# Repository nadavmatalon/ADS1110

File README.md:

# ADS1110 DRIVER

&nbsp;&nbsp;&nbsp;&nbsp;&nbsp;&nbsp;&nbsp;&nbsp;&nbsp;&nbsp;

&nbsp;&nbsp;&nbsp;&nbsp;&nbsp;&nbsp;&nbsp;&nbsp;&nbsp;&nbsp;

&nbsp;&nbsp;&nbsp;&nbsp;&nbsp;&nbsp;&nbsp;&nbsp;&nbsp;&nbsp;

The ADS1110 is a 16-Bit Single-Channel (Single-Ended or Differential) ADC with Onboard Reference (2.048V), PGA & HW I2C capabilities.

This library contains a complete driver for the ADS1110 offering full control over its Configuration Settings, as well as the ability to recieve raw data, voltage readings (in mV, to avoid floating point math) or percentage readings in either Single-Shot or Continuous mode.

Source: [ADS1110 DATASHEET](http://www.ti.com/lit/ds/symlink/ads1110.pdf)

## Repository Contents

- **ADS1110.h** - Library Header file.
- **ADS1110.cpp** - Library Compilation.
- **/utility** 
  - **ADS1110InfoStr.h** - Header file containing a functional extention of the library to include generating printable information String (see Note #5 below).
  - **ADS1110ComStr.h** - Header file containing a functional extention of the library to include generating a printable I2C Communication Result String (see Note #6 below).
  - **ADS1110_PString.h** - Header file for PString class (lighter alternative to String class) 
  - **ADS1110_PString.cpp** - Compilation file for PString class (lighter alternative to String class) 
- **/examples**   
  - **/ADS1110_Test**
    - **ADS1110_Test.ino** - A basic sketch for testing whether the ADS1110 is hooked-up and operating correctly.
  - **/ADS1110_Usage**
    - **ADS1110_Usage.ino** - A much more extensive sketch offering a complete usage illustration, as well as a rubust testing mechanism.
  - **/ADS1110_Info** 
    - **ADS1110_Info.ino** - A short sketch showing how to generate a Printable Device Information String of the ADS1110's current settings (i.e. Configuration, Limit &anp; Hysteresis registers, etc.).
  - **/ADS1110_I2C_Status**
    - **ADS1110_I2C_Status.ino** - A short sketch for verifying I2C communication has been established between the controller and the ADS1110.
- **/extras**
  - **License.txt** - A cope of the end-user license agreement.  
  - **/eagle**
    - **ADS1110.sch** - Schematic file for the ADS1110 breakout board.
    - **ADS1110.brd** - Board layout file for the ADS1110 breakout board.
  - **/images**
    - **ads1110_pinout.png** - Pinout image of the ADS1110.
- **keywords.txt** - Keywords for this library which will be highlighted in sketches within the Arduino IDE. 
- **library.properties** - General library properties for the Arduino's IDE (>1.5) Library Package Manager.
- **README.md** - The readme file for this library.
- **library.json** - JSON file for the Arduino's IDE (>1.5) Package Manager.

## HOOK-UP

* __PIN 1 (Vin+)__ - Connect Vin+ to voltage source to be measured
* __PIN 2 (GND)__ - Connect GND to Arduino GND
* __PIN 3 (SCL)__ - Connect to Arduino PIN A5 with a 2K2 pull-up resistor
* __PIN 4 (SDA)__ - Connect to the Arduino's PIN A5 with a 2K2 pull-up resistor
* __PIN 5 (VCC)__ - Connect VCC to Arduino 5V output
* __PIN 6 (Vin-)__ - Connect Vin- either to Arduino GND (for Single-Ended voltage readings ranging 0-2.048V) or to an external 2.048V reference source (for Single-Ended voltage readings ranging 0-4.096V) or to 'negative' input (for differential voltage readings between positive and 'negative' inputs).
* __DECOUPING__: Connect a 0.1uF Ceramic Capacitor between the ADS1110's VCC &amp; GND PINS

>__Note__: The 'negative' of input Vin- is put in brackets here because it actually differential in nature and not a so-called real negative voltage - 
that is, it's negative only with relation to the positive input side of Vin+.

## GENERAL NOTES

1) __I2C Communications Library Dependency__

This library depends on the Arduino IDE's native '[Wire](https://github.com/arduino/Arduino/tree/master/hardware/arduino/avr/libraries/Wire)' library for I2C communication between the Arduino (Master) and the ADS1110 (Slave). 

2) __Dangers of GAIN Setting__

As I've managed to fry 2 ADS1110 ICs by changing the GAIN settings from the default x1 to another value, I've decided to stay away from this particular setting and not to include it in the full usage/testing sketch. That said, the library does contain the relevant functions for getting/setting the GAIN, however, make sure you know what you're doing when fiddling with this as you may damage your device.

3) __Voltage Reference Settings__

To get the correct __Raw Data Reading__/__Voltage Readings__/__Percentage Readings__, it is crucial to have the __Voltage Reference (Vref)__ setting defined correctly (i.e. INTERNAL / EXTERNAL). This is done on the basis of the physical hookup of the ADS1110's pin Vin- (namely: INTERNAL if this pin goes to GND, or EXTERNAL if it goes to an 2.048V external source. The default is GND connection &amp; an INTERNAL settings definition).  

4) __Sample Rate &amp; Resolution Interdependence__

The ADS1110's __Sample Rate__ and __Resolution__ settings are interdependent, that is, setting the value of one will automatically cause the other to change accordingly (15_SPS = 16-BIT / 30_SPS = 15-BIT / 60_SPS = 14-BIT / 240_SPS = 12-BIT).  

5) __Device Information String__

It possible to extend the ADS1110 Library to include a function for generating a printable device information string showing all the relevant details about the devices current Configuration, Limit & Hysteresis settings. As the additional functionality comes at the cost of increased memory footprint, it was implemented as an optional add-on rather than added directly to the core ADS1110 Library. See the [ADS1110_Info](https://github.com/nadavmatalon/ADS1110/blob/master/examples/ADS1110_Info/ADS1110_Info.ino) example sketch for detailed explanation and an actual usage demo.

6) __Device I2C Communications String__

It is also possible to extend the ADS1110 Library to include a function for generating a printable I2C Communications string showing the result of each I2C transaction in a human-friendly way, something that may be useful, for example, during debugging sessions. As the additional functionality comes at the cost of increased memory footprint, it was implemented as an optional add-on rather than added directly to the core ADS1110 Library. See the [ADS1110_I2C_Status](https://github.com/nadavmatalon/ADS1110/blob/master/examples/ADS1110_I2C_Status/ADS1110_I2C_Status.ino) example sketch for detailed explanation and an actual usage demo.

## I2C ADDRESSES

Each ADS1110 has 1 of 8 possible I2C addresses (factory hardwired &amp; recognized by its specific part number & top marking on the package itself):

| PART NO.  | BIN     | HEX  | DEC | MARKING |
|-----------|---------|------|-----|---------|
| ADS1110A0 | 1001000 | 0x48 | 72  | ED0     |
| ADS1110A1 | 1001001 | 0x49 | 73  | ED1     |
| ADS1110A2 | 1001010 | 0x4A | 74  | ED2     |
| ADS1110A3 | 1001011 | 0x4B | 75  | ED3     |
| ADS1110A4 | 1001100 | 0x4C | 76  | ED4     |
| ADS1110A5 | 1001101 | 0x4D | 77  | ED5     |
| ADS1110A6 | 1001110 | 0x4E | 78  | ED6     |
| ADS1110A7 | 1001111 | 0x4F | 79  | ED7     |

## LIBRARY INSTALLATION & SETUP

Begin by installing the library either by using the Arduino IDE's Installation Wizard (Arduino Version >1.5) or simply download the library's ZIP folder from GITHUB, extract it, and copy the extraxcted folder to your Arduino 'libraries' folder.

Next, include the library at the top of the sketch as follows:

```
#include "ADS1110.h"
```

At this point you can construct a new ADS1110 object(s) by using the following command (at the top of the sketch after the 'include' line):

```
ADS1110 device_name(device_address);
```

>Replace '__device_name__' with a name of your choice. Also, make sure to replace the variable '__device_address__' with 
the specific I2C address of your device if needed (see I2C ADDRESSES section above).

Next, make sure to inlude an instruction for initializing the I2C Bus for the [Wire](https://github.com/arduino/Arduino/tree/master/hardware/arduino/avr/libraries/Wire) Library, as follows:

(There's no need to include the [Wire](https://github.com/arduino/Arduino/tree/master/hardware/arduino/avr/libraries/Wire) Library at the top of the sketch as it's already included by the present library)

```
void setup() {
    Wire.begin();
    // ...other setup code...
}
```

## LIBRARY FUNCTIONS

With the library installed &amp; included in the sketch, and an ADS1110 object initiallized, the following functions are available (see the usage example sketch for a detailed implementation):

__Note About Methods' Return Values:__  
All 'get' methods return some sort of value (e.g. getGain(), getMode() etc.), while all 'set' methods return nothing. Nevertheless, ALL methods implicitly update the library's __I2C _comBuffer__ (=communication buffer) after each I2C transmission. The reason for this functional design is to maintain structural coherance between the 'get' and 'set' methods. As 'get' methods cannot return both the desired value and the I2C transmission's result simultaniously. Consequently, if the relevant value hasn't been obtained by a particular 'get' method, the user can simply check the content of the _comBuffer to see what error occured. Similarly, it is possible to check if a particular setting has been successfully applied via a 'set' method either by preforming the corresponding 'get' method or by checking the content of the _comBuffer (0 indicates a successful transmission, 1-6 indicate an error as listed below). 

__ping();__                                    
Parameters:&nbsp;&nbsp;&nbsp;None  
Description:&nbsp;&nbsp;&nbsp;Searches for the ADS1110 at the pre-defined I2C Bus address &amp; returns byte with the relevant success/error code, as follows:  
0  ...  Success (no error)  
1  ...  Buffer overflow  
2  ...  Address sent, NACK received  
3  ...  Data send, NACK received  
4  ...  Other error (lost bus arbitration, bus error, etc.)  
5  ...  Timed-out while trying to become Bus Master  
6  ...  Timed-out while waiting for data to be sent  
\>6 ... Unlisted error (potential future implementation/s)<br>
Returns:&nbsp;&nbsp;&nbsp;&nbsp;&nbsp;&nbsp;&nbsp;&nbsp;&nbsp;byte  
  
__getGain();__  
Parameters:&nbsp;&nbsp;&nbsp;None  
Description:&nbsp;&nbsp;&nbsp;Gets the current Gain settings (x1 [Default] / x2 / x4 / x8)  
Returns:&nbsp;&nbsp;&nbsp;&nbsp;&nbsp;&nbsp;&nbsp;&nbsp;Byte  
  
__getSampleRate();__  
Parameters:&nbsp;&nbsp;&nbsp;None  
Description:&nbsp;&nbsp;&nbsp;Gets the current Sample Rate settings  (15 SPS [Default] / 30 SPS / 60 SPS / 240 SPS)  
Returns:&nbsp;&nbsp;&nbsp;&nbsp;&nbsp;&nbsp;&nbsp;&nbsp;Byte  
  
__getConMode();__  
Parameters:&nbsp;&nbsp;&nbsp;None  
Description:&nbsp;&nbsp;&nbsp;Gets the current Conversion Mode settings (0 = CONTINUOUS [Default] / 1 = SINGLE-SHOT)  
Returns:&nbsp;&nbsp;&nbsp;&nbsp;&nbsp;&nbsp;&nbsp;&nbsp;Byte  
  
__getRes();__  
Parameters:&nbsp;&nbsp;&nbsp;None  
Description:&nbsp;&nbsp;&nbsp;Gets the current Resolution settings (12-BIT / 14-BIT / 15-BIT / 16-BIT [Default])  
Returns:&nbsp;&nbsp;&nbsp;&nbsp;&nbsp;&nbsp;&nbsp;&nbsp;Byte  
  
__getVref();__  
Parameters:&nbsp;&nbsp;&nbsp;None  
Description:&nbsp;&nbsp;&nbsp;Gets the current Voltage Reference mode (0 = INTERNAL [Default] / 2048 = EXTERNAL)  
Returns:&nbsp;&nbsp;&nbsp;&nbsp;&nbsp;&nbsp;&nbsp;&nbsp;Int  
  
__setGain();__  
Parameters:&nbsp;&nbsp;&nbsp;GAIN_1 / GAIN_2 /GAIN_4 / GAIN_8  
Description:&nbsp;&nbsp;&nbsp;Sets the Gain (x1 / x2 / x4 / x8)  
Returns:&nbsp;&nbsp;&nbsp;&nbsp;&nbsp;&nbsp;&nbsp;&nbsp;None  
  
__setSampleRate();__  
Parameters:&nbsp;&nbsp;&nbsp;SPS_15 / SPS_30 / SPS_60 / SPS_240  
Description:&nbsp;&nbsp;&nbsp;Sets the Sample Rate in Samples per Second (15 SPS / 30 SPS / 60 SPS / 240 SPS)  
Returns:&nbsp;&nbsp;&nbsp;&nbsp;&nbsp;&nbsp;&nbsp;&nbsp;None  
  
__setConMode();__  
Parameters:&nbsp;&nbsp;&nbsp;CONT / SINGLE  
Description:&nbsp;&nbsp;&nbsp;Sets the Conversion Mode (CONTINUOUS / SINGLE-SHOT)  
Returns:&nbsp;&nbsp;&nbsp;&nbsp;&nbsp;&nbsp;&nbsp;&nbsp;None  
  
__setRes();__  
Parameters:&nbsp;&nbsp;&nbsp;12_BIT / 14_BIT / 15_BIT / 16_BIT  
Description:&nbsp;&nbsp;&nbsp;Sets the Resolution level ( 12-BIT / 14-BIT / 15-BIT / 16-BIT)  
Returns:&nbsp;&nbsp;&nbsp;&nbsp;&nbsp;&nbsp;&nbsp;&nbsp;None  
  
__setVref();__  
Parameters:&nbsp;&nbsp;&nbsp;INT_REF / EXT_REF  
Description:&nbsp;&nbsp;&nbsp;Sets the Voltage reference mode (INTERNAL / EXTERNAL)  
This setting needs to be set according to the hardware hookup of the ADS1110 Pin Vin-, namely: If the Vin- pin is connected to GND, then the Voltage Reference (Vref) should be set to 'INTERNAL'. This, in turn, provides a voltage reading range of 0-2048mV. Alternatively, the Vin- pin may be connected to an external 2.048V source, in which case the Voltage Referece settings should be set to 'EXTERNAL'. The latter hookup & setting gives an extended voltage reading range of 0-4096mV.  
Returns:&nbsp;&nbsp;&nbsp;&nbsp;&nbsp;&nbsp;&nbsp;&nbsp;None  
  
__reset();__  
Parameters:&nbsp;&nbsp;&nbsp;None  
Description:&nbsp;&nbsp;&nbsp;Resets the Configuration register to its default settings  
Returns:&nbsp;&nbsp;&nbsp;&nbsp;&nbsp;&nbsp;&nbsp;&nbsp;None  
  
__getData();__  
Parameters:&nbsp;&nbsp;&nbsp;None  
Description:&nbsp;&nbsp;&nbsp;Gets the latest raw ADC reading  
Returns:&nbsp;&nbsp;&nbsp;&nbsp;&nbsp;&nbsp;&nbsp;&nbsp;Int  
  
__getVolt();__  
Parameters:&nbsp;&nbsp;&nbsp;None  
Description:&nbsp;&nbsp;&nbsp;Gets the latest ADC reading (in mV, to avoid floating point calculations)  
Returns:&nbsp;&nbsp;&nbsp;&nbsp;&nbsp;&nbsp;&nbsp;&nbsp;Int  
  
__getPercent();__  
Parameters:&nbsp;&nbsp;&nbsp;None  
Description:&nbsp;&nbsp;&nbsp;Gets the latest ADC reading in Percentage format (0-100%)  
Returns:&nbsp;&nbsp;&nbsp;&nbsp;&nbsp;&nbsp;&nbsp;&nbsp;Byte  
  
__getComResult();__  
Parameters:&nbsp;&nbsp;&nbsp;None  
Description:&nbsp;&nbsp;Returns the latest I2C Communication result code (see Success/Error codes above)  
Returns:&nbsp;&nbsp;&nbsp;&nbsp;&nbsp;&nbsp;&nbsp;&nbsp;byte  
  
__Destructor__  
If you want to destruct an instantiated ADS1110 object, you can use the following method to do so:  

```
~ADS1110 device_name();
```
>Replace '__device_name__' with the name of your ADS1110 device.

## Extended Functionality*

(* requires an additional '\#include' of the relevant *.h file as shown in the corresponding example sketches)  
  
__ADS1110ComStr();__  
Parameters:&nbsp;&nbsp;&nbsp;Name of an initialized ADS1110 instance  
Description:&nbsp;&nbsp;Returns printable string containing human-friendly information about the device's latest I2C communication result  
Returns:&nbsp;&nbsp;&nbsp;&nbsp;&nbsp;&nbsp;&nbsp;&nbsp;PString  
  
__ADS1110InfoStr();__  
Parameters:&nbsp;&nbsp;&nbsp;Name of an initialized ADS1110 instance  
Description:&nbsp;&nbsp;Returns printable string containing detailed information about the device's current settings  
Returns:&nbsp;&nbsp;&nbsp;&nbsp;&nbsp;&nbsp;&nbsp;&nbsp;PString  

## RUNNING THE EXAMPLE SKETCHES
  
1) Start the Arduino IDE and open the relevant example sketch  
2) Hook-up the ADS1110 to the Arduino as explained in the sketch's notes   
3) Upload the sketch to the Arduino  
4) Open the Serial Communications Window (make sure the baud-rate is set to 9600 or change it in the sketch to match your Serial Port's buad-rate)  
  
## BUG REPORTS
  
Please report any issues/bugs/suggestions at the [Issues](https://github.com/nadavmatalon/ADS1110/issues) section of this Github repository.
  
## TODO
  
* __CORE LIBRARY__: Add running average functionality  
  
## VERSION HISTORY

__Ver. 1.0.0__ - First release (26.9.16)  
__Ver. 1.1.0__ - Major code refactoring (10.10.16)  
__Ver. 1.2.0__ - Added namespaces to prevent conflicts with other libraries (15.10.16)  
__Ver. 1.3.0__ - Switched from 'WSWire' library to 'Wire' library for I2C communications (24.10.16)

## LICENSE

[The MIT License (MIT)](https://opensource.org/licenses/MIT)
Copyright (c) 2016 Nadav Matalon

Permission is hereby granted, free of charge, to any person obtaining a copy of this software and associated documentation files (the "Software"), to deal in the Software without restriction, including without limitation the rights to use, copy, modify, merge, publish, distribute, sublicense, and/or sell copies of the Software, and to permit persons to whom the Software is furnished to do so, subject to the following conditions:

The above copyright notice and this permission notice shall be included in all copies or substantial portions of the Software.

THE SOFTWARE IS PROVIDED "AS IS", WITHOUT WARRANTY OF ANY KIND, EXPRESS OR IMPLIED, INCLUDING BUT NOT LIMITED TO THE WARRANTIES OF MERCHANTABILITY, FITNESS FOR A PARTICULAR PURPOSE AND NONINFRINGEMENT. IN NO EVENT SHALL THE AUTHORS OR COPYRIGHT HOLDERS BE LIABLE FOR ANY CLAIM, DAMAGES OR OTHER LIABILITY, WHETHER IN AN ACTION OF CONTRACT, TORT OR OTHERWISE, ARISING FROM, OUT OF OR IN CONNECTION WITH THE SOFTWARE OR THE USE OR OTHER DEALINGS IN THE SOFTWARE.

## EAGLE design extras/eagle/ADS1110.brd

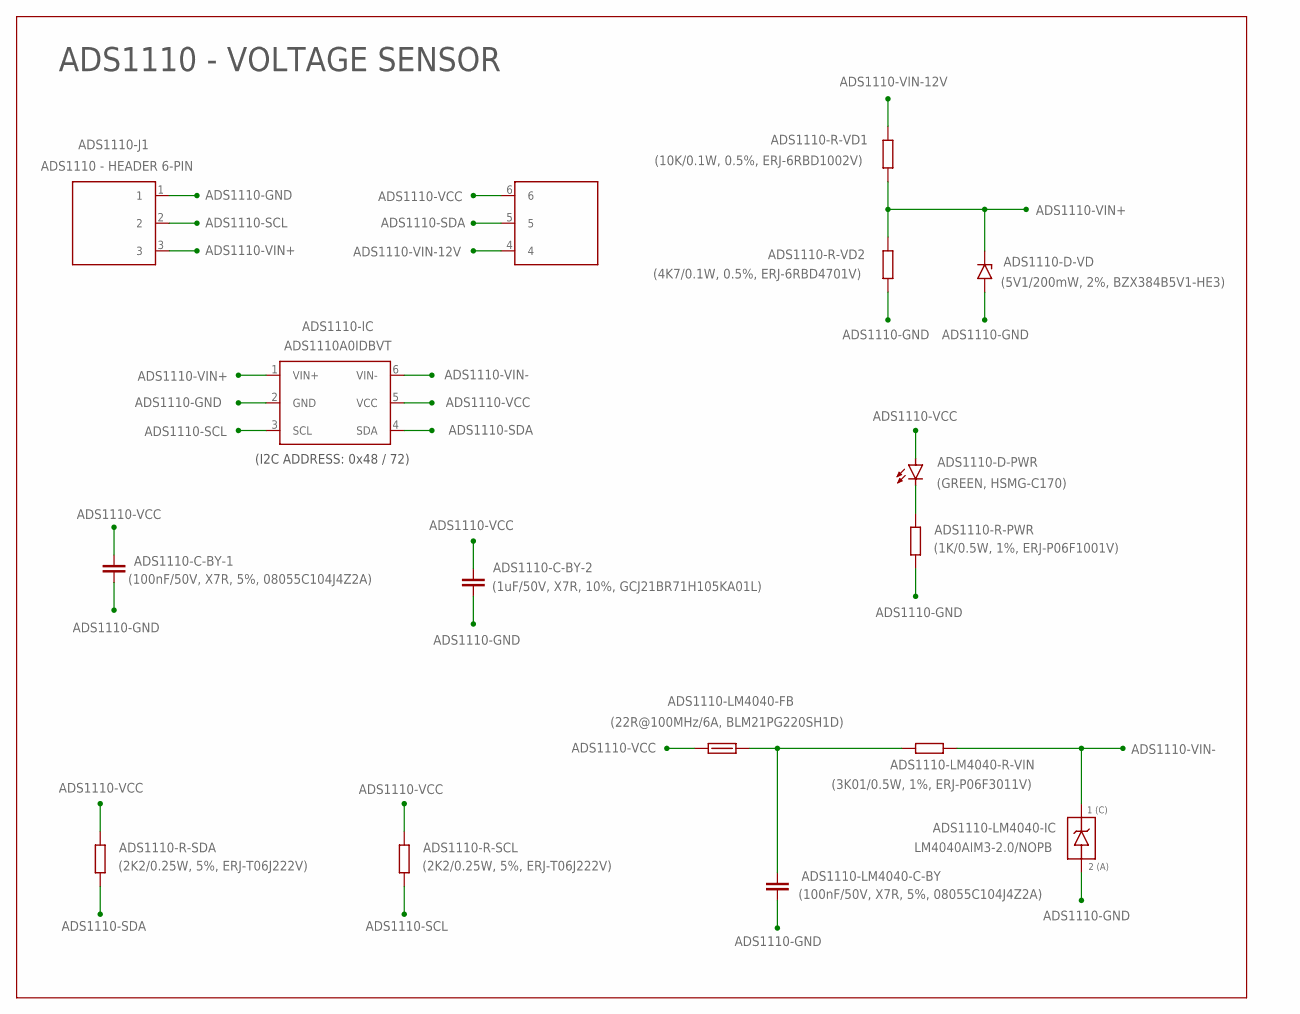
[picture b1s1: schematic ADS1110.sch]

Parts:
ADS1110-C-BY-1, ADS1110-LM4040-C-BY: (100nF/50V, X7R, 5%, 08055C104J4Z2A); 0805
ADS1110-C-BY-2: (1uF/50V, X7R, 10%, GCJ21BR71H105KA01L); 0805
ADS1110-D-PWR: (GREEN, HSMG-C170); DIODE_0805
ADS1110-D-VD: (5V1/200mW, 2%, BZX384B5V1-HE3); SOD-323-DIODE
ADS1110-IC: ADS1110A0IDBVT; SOT-457-6
ADS1110-J1: ADS1110 - HEADER 6-PIN; HEADER_2.54MM_6_PIN_VER
ADS1110-LM4040-FB: (22R@100MHz/6A, BLM21PG220SH1D); 0805
ADS1110-LM4040-IC: LM4040AIM3-2.0/NOPB; SOT-23-3
ADS1110-LM4040-R-VIN: (3K01/0.5W, 1%, ERJ-P06F3011V); 0805
ADS1110-R-PWR: (1K/0.5W, 1%, ERJ-P06F1001V); 0805
ADS1110-R-SCL, ADS1110-R-SDA: (2K2/0.25W, 5%, ERJ-T06J222V); 0805
ADS1110-R-VD1: (10K/0.1W, 0.5%, ERJ-6RBD1002V); 0805
ADS1110-R-VD2: (4K7/0.1W, 0.5%, ERJ-6RBD4701V); 0805

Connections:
ADS1110-GND: ADS1110-C-BY-1.2 (C), ADS1110-C-BY-2.1 (A), ADS1110-D-VD.A, ADS1110-IC.2 (GND), ADS1110-J1.1, ADS1110-LM4040-C-BY.2 (C), ADS1110-LM4040-IC.2 (A), ADS1110-LM4040-IC.3 (A), ADS1110-R-PWR.1, ADS1110-R-VD2.2
ADS1110-LED-PWR: ADS1110-D-PWR.C, ADS1110-R-PWR.2
ADS1110-SCL: ADS1110-IC.3 (SCL), ADS1110-J1.2, ADS1110-R-SCL.1
ADS1110-SDA: ADS1110-IC.4 (SDA), ADS1110-J1.5, ADS1110-R-SDA.1
ADS1110-VCC: ADS1110-C-BY-1.1 (A), ADS1110-C-BY-2.2 (C), ADS1110-D-PWR.A, ADS1110-IC.5 (VCC), ADS1110-J1.6, ADS1110-LM4040-FB.2, ADS1110-R-SCL.2, ADS1110-R-SDA.2
ADS1110-VCC-FILTERED: ADS1110-LM4040-C-BY.1 (A), ADS1110-LM4040-FB.1, ADS1110-LM4040-R-VIN.2
ADS1110-VIN+: ADS1110-D-VD.C, ADS1110-IC.1 (VIN+), ADS1110-J1.3, ADS1110-R-VD1.2, ADS1110-R-VD2.1
ADS1110-VIN-: ADS1110-IC.6 (VIN-), ADS1110-LM4040-IC.1 (C), ADS1110-LM4040-R-VIN.1
ADS1110-VIN-12V: ADS1110-J1.4, ADS1110-R-VD1.1

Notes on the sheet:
(I2C ADDRESS: 0x48 / 72)
ADS1110 - VOLTAGE SENSOR

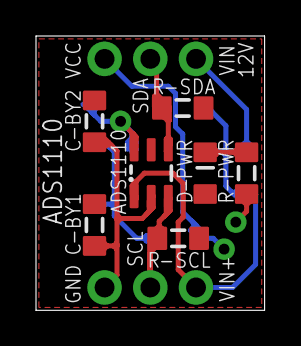
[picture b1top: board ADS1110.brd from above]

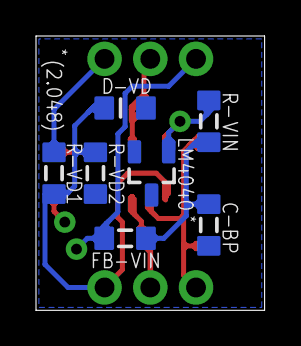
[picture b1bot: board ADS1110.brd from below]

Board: 2 copper layers, 12.7 x 15.2 mm, 15 parts (7 on the bottom side), 9 nets.

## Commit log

2016-08-11 Properties file update
2016-08-20 Major Re-Write
2016-08-20 Added initial device testing sketch
2016-08-20 Minor naming change
2016-08-20 Added test sketch and minor changes
2016-08-21 Another round of refactoring
2016-08-23 Another round of refactoring and documentation updates
2016-08-23 Minor correction to method descriptions
2016-08-23 Further minor correction to method descriptions
2016-08-23 Minor correction of I2C Communication Codes list
2016-08-23 Added link to the Bug Report section
2016-08-23 Fixed link to the Bug Report section
2016-08-23 Updated descriptions
2016-08-23 Formating correction
2016-10-11 major code refactoring
2016-10-11 Added entry to list of I2C communication codes
2016-10-12 major code refacrtoring
2016-10-13 added items to TODO list
2016-10-14 corrected typo
2016-10-14 corrected formatting
2016-10-15 added namespaces to prevent conflicts with other libraries
2016-10-18 added initializer to _cmBuffer
2016-10-19 changed I2C address and number of bytes request to byte type variable. Updated examples
2016-10-20 updated minor version number in version badge
2016-10-20 added Eagle breakout board design for the ADS1110
2016-10-20 added eagle pcb badge
2016-10-21 minor changes in getData function
2016-10-24 Switched from WSWire to Wire for I2C communication
2016-10-24 updated title
2016-10-24 cosmetic fixes
2016-10-24 cosmetic fix
2016-10-24 added .gitattributes file
2016-10-28 updated documentation
2016-12-06 added pinout image

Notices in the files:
README.md:
Copyright (c) 2016 Nadav Matalon
Permission is hereby granted, free of charge, to any person obtaining a copy of this software and associated documentation files (the "Software"), to deal in the Software without restriction, including without limitation the rights to use, copy, modify, merge, publish, distribute, sublicense, and/or sell copies of the Software, and to permit persons to whom the Software is furnished to do so, subject to the following conditions:
The above copyright notice and this permission notice shall be includ
